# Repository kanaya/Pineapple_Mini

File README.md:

# Pineapple Mini

Pineapple Mini is a MIDI-connected relay driver. Please read doc/pineapple_mini.md for more info.

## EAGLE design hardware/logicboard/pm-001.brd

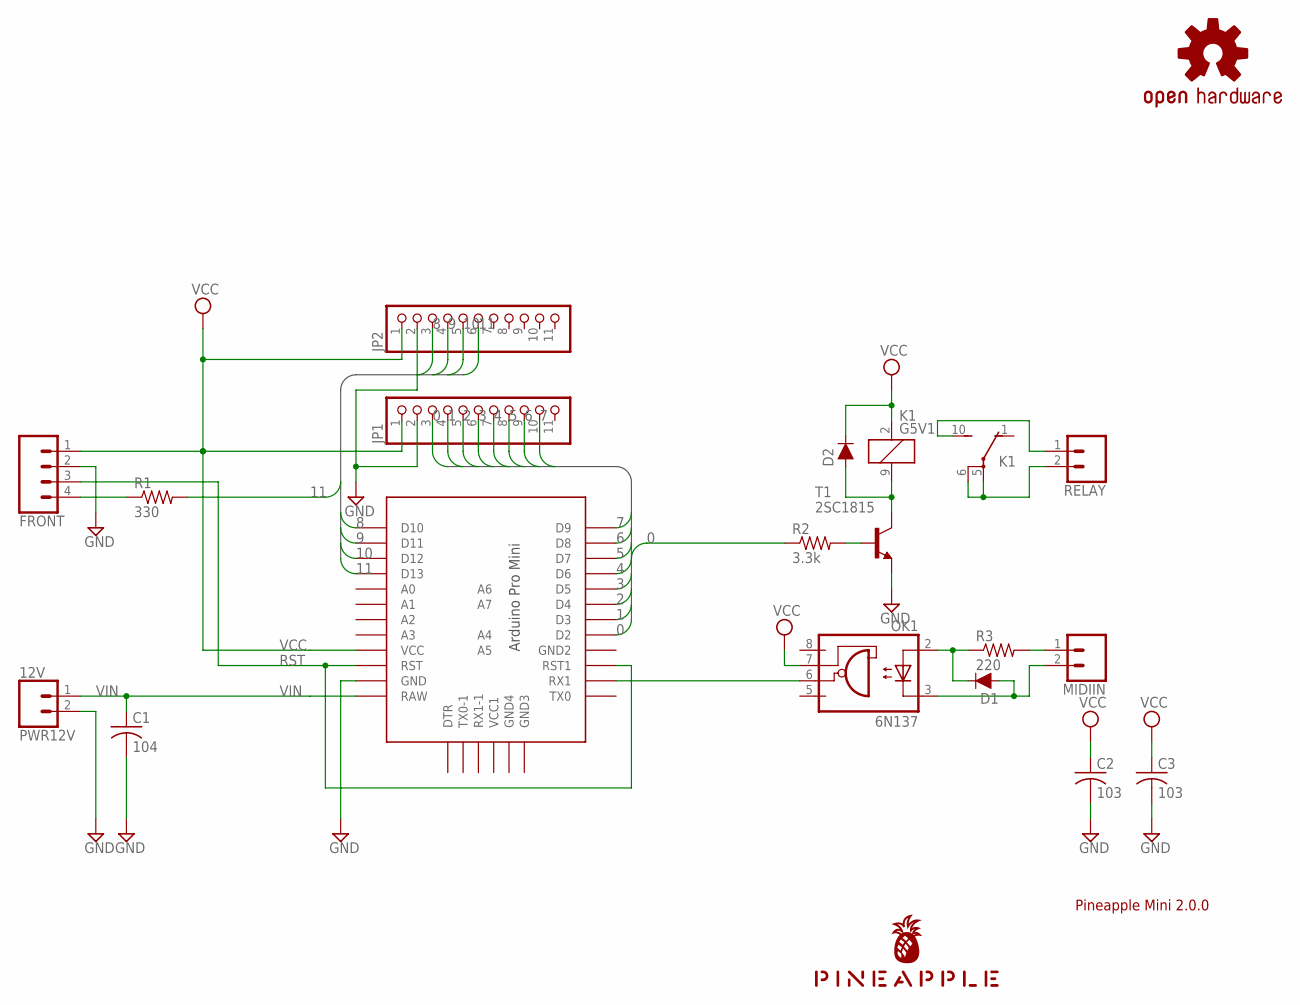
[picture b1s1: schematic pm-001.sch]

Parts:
C1: 104; C025-025X050
C2, C3: 103; C025-025X050
D1, D2: DIODE-1N4148
FRONT: CONN_04JST-PTH; JST-4-PTH
JP1, JP2: PINHD-1X11; 1X11
K1: G5V1
LOGO1: OSHW-LOGOS-COPPER; OSHW-LOGO-S_COPPER
MIDIIN: CONN_02JST-PTH-2; JST-2-PTH
OK1: 6N137; DIL08
PWR12V: 12V; JST-2-PTH
R1: 330; 0204/5
R2: 3.3k; 0204/5
R3: 220; 0204/5
RELAY: CONN_02JST-PTH-2; JST-2-PTH
T1: 2SC1815; TO92-ECB
U$1: PRO-MINI-2
U$2: PINEAPPLE450

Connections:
0: JP1.3, R2.1, U$1.D2
0R: R2.2, T1.B
1: JP1.4, U$1.D3
2: JP1.5, U$1.D4
3: JP1.6, U$1.D5
4: JP1.7, U$1.D6
5: JP1.8, U$1.D7
6: JP1.9, U$1.D8
7: JP1.10, U$1.D9
8: JP2.3, U$1.D10
9: JP2.4, U$1.D11
10: JP2.5, U$1.D12
11: JP2.6, R1.2, U$1.D13
GND: C1.2, C2.2, C3.2, FRONT.2, JP1.2, JP2.2, PWR12V.2, T1.E, U$1.GND
INDR: FRONT.4, R1.1
MIDIIN: OK1.6 (VO), U$1.RX1
MIDIIN+: MIDIIN.1, R3.2
MIDIIN-: D1.A, MIDIIN.2, OK1.3 (C)
MIDIINA: D1.C, OK1.2 (A), R3.1
RELAYA: K1.10 (S), RELAY.1
RELAYB: K1.5, K1.6, RELAY.2
RELAYC: D2.A, K1.9 (2), T1.C
RST: FRONT.3, U$1.RST, U$1.RST1
VCC: C2.1, C3.1, D2.C, FRONT.1, JP1.1, JP2.1, K1.2 (1), OK1.7 (VE), U$1.VCC
VIN: C1.1, PWR12V.1, U$1.RAW

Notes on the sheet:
Pineapple Mini 2.0.0

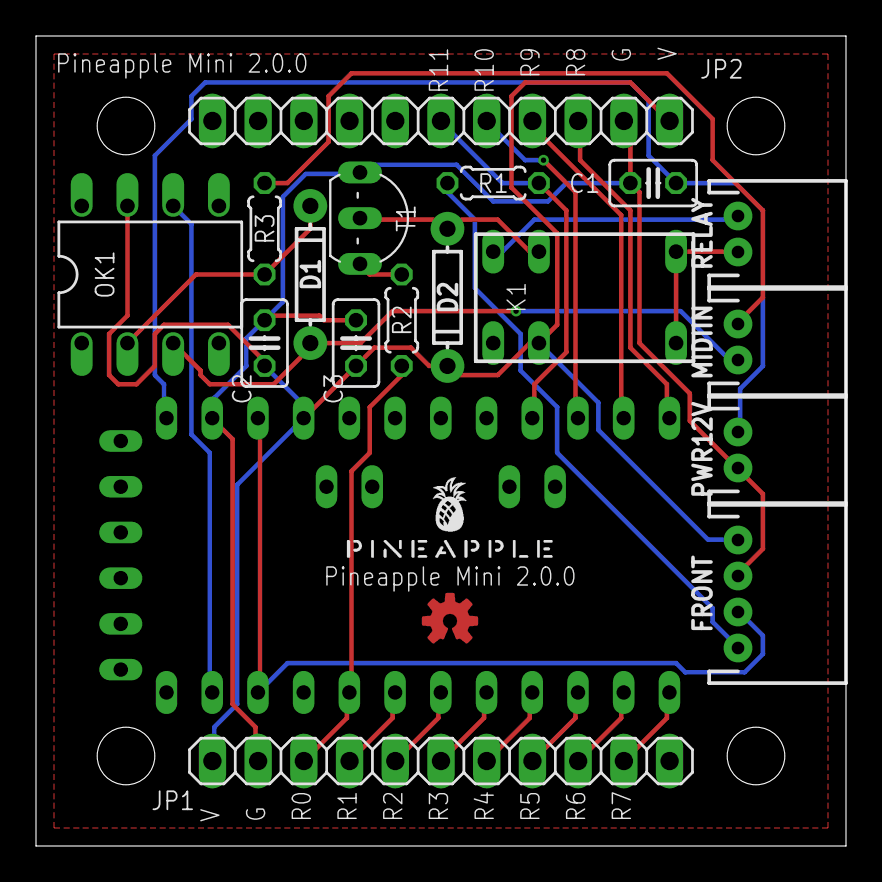
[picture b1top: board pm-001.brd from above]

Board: 2 copper layers, 45.0 x 45.0 mm, 20 parts (0 on the bottom side), 25 nets.

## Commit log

2018-07-29 New design.
2018-07-29 gitignore.
2018-07-29 CAM files.
2018-07-29 FTDI.
2018-08-03 Clean up.
2018-08-03 .gitignore.
2018-08-04 1mm exterior.
2018-08-05 Fixed edges.
2018-08-10 1mm-exterior.
2018-08-10 Document update.
2018-08-10 Moved the processor slightly so that FTDI adapter easily fits.
2018-08-10 D8 -> D2.
2018-08-10 Sockets for stacking.
2018-08-10 Silk.
2018-08-10 Moved FTDI connector to stackable position.
2018-08-10 Doc.
2018-08-10 Fine tuning of the position of Arduino Pro Mini.
2018-08-10 Reversed direction of JP2.
2018-08-11 OSHW logo.
2018-08-13 Pineapple logo v2.
2018-08-13 New pineapple logo.
2018-08-14 Updated silk patterns and signal names.
2018-08-14 Changed signal names.
2018-08-14 Adde Makefile.
2018-08-14 Fixed Makefile.
2018-08-21 Pineapple Logo (vector->bitmap), OSHW logo (silk -> copper).
2018-08-21 Removed "Rev." from silk pattern.
2018-08-22 Changed font size of the silk pattern.

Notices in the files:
parts and their libraries:
SparkFun-Connectors: Licensing: Creative Commons ShareAlike 4.0 International - https://creativecommons.org/licenses/by-sa/4.0
